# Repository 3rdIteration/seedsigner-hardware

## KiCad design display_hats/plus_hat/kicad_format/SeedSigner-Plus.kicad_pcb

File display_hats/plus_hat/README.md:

# SeedSigner Plus Display Hat

## Supporting the Project
If you are producing these to sell, please consider donating X per board to Y to support the project.

## Design Files
The files used to produce the original SeedSigner+ hat can be found in the `designspark_format` folder. This also includes production files that can be used to have the board fabricated.

A version in KiCAD format can also be found in the `kicad_format` folder along with all he files needed for low-cost economic fabrication with JLCPCB. (Very low cost if you are happy have one side assembled and manually solder the buttons on)

## LCD Display

The current design assumes LCD available here: https://www.alibaba.com/x/B1E3wJ

**LCD Specifications**
* Size: 2.8 inch
* LCD Type: IPS (A TFT cheaper TFT panel will work, but has a smaller viewing angle)
* Outline Dimensions: 47.8*66.95*2.13mm
* Number of Dots: 240(RGB)*320
* Controller: ST7789
* PIN NO.: 40P
* Display Color: RGB565
* Backlight: White LED
* Polarizer Mode: Transmissive
* Data Interface: 3/4-Wire SPI interface, MCU 8/16Bit interface
* Operating Temp.: -20 ~ 70 degree
* Storage Temp.: -30 ~ 80 degree
* Viewing Direction: 12 O’clock / Full

**Pinout for Display**
| PIN | Symbol        | Notes                                                     |
| --: | ------------- | --------------------------------------------------------- |
|   1 | XL / X−       | Resistive touch X− electrode (if resistive touch is used) |
|   2 | YU / Y−       | Resistive touch Y− electrode                              |
|   3 | XR / X+       | Resistive touch X+ electrode                              |
|   4 | YD / Y+       | Resistive touch Y+ electrode                              |
|   5 | GND           | Ground                                                    |
|   6 | VDD           | Logic supply voltage (typically 3.3 V)                    |
|   7 | VDD           | Logic supply voltage (typically 3.3 V)                    |
|   8 | TE            | Tearing Effect output (optional, frame sync signal)       |
|   9 | CSX / SPI_CS  | Chip Select for SPI or parallel interface                 |
|  10 | DCX / SPI_SCL | Data/Command select (SPI clock in SPI mode)               |
|  11 | WRX / SPI_DCX | Write strobe (parallel) or Data/Command in SPI            |
|  12 | RDX           | Read strobe (parallel interface only)                     |
|  13 | SPI_MOSI      | SPI Master Out / Slave In                                 |
|  14 | SPI_MISO      | SPI Master In / Slave Out                                 |
|  15 | RESX          | Hardware reset (active low)                               |
|  16 | GND           | Ground                                                    |
|  17 | DB0           | Parallel data bus bit 0                                   |
|  18 | DB1           | Parallel data bus bit 1                                   |
|  19 | DB2           | Parallel data bus bit 2                                   |
|  20 | DB3           | Parallel data bus bit 3                                   |
|  21 | DB4           | Parallel data bus bit 4                                   |
|  22 | DB5           | Parallel data bus bit 5                                   |
|  23 | DB6           | Parallel data bus bit 6                                   |
|  24 | DB7           | Parallel data bus bit 7                                   |
|  25 | DB8           | Parallel data bus bit 8                                   |
|  26 | DB9           | Parallel data bus bit 9                                   |
|  27 | DB10          | Parallel data bus bit 10                                  |
|  28 | DB11          | Parallel data bus bit 11                                  |
|  29 | DB12          | Parallel data bus bit 12                                  |
|  30 | DB13          | Parallel data bus bit 13                                  |
|  31 | DB14          | Parallel data bus bit 14                                  |
|  32 | DB15          | Parallel data bus bit 15                                  |
|  33 | LED-A         | Backlight LED anode (usually requires current driver)     |
|  34 | LED-K         | Backlight LED cathode                                     |
|  35 | LED-K         | Backlight LED cathode                                     |
|  36 | LED-K         | Backlight LED cathode                                     |
|  37 | GND           | Ground                                                    |
|  38 | IM0           | Interface mode select (sampled on reset)                  |
|  39 | IM1           | Interface mode select (sampled on reset)                  |
|  40 | IM2           | Interface mode select (sampled on reset)                  |

**Note: The Pin numbering on the FPC connector is in reverse order to the list above**

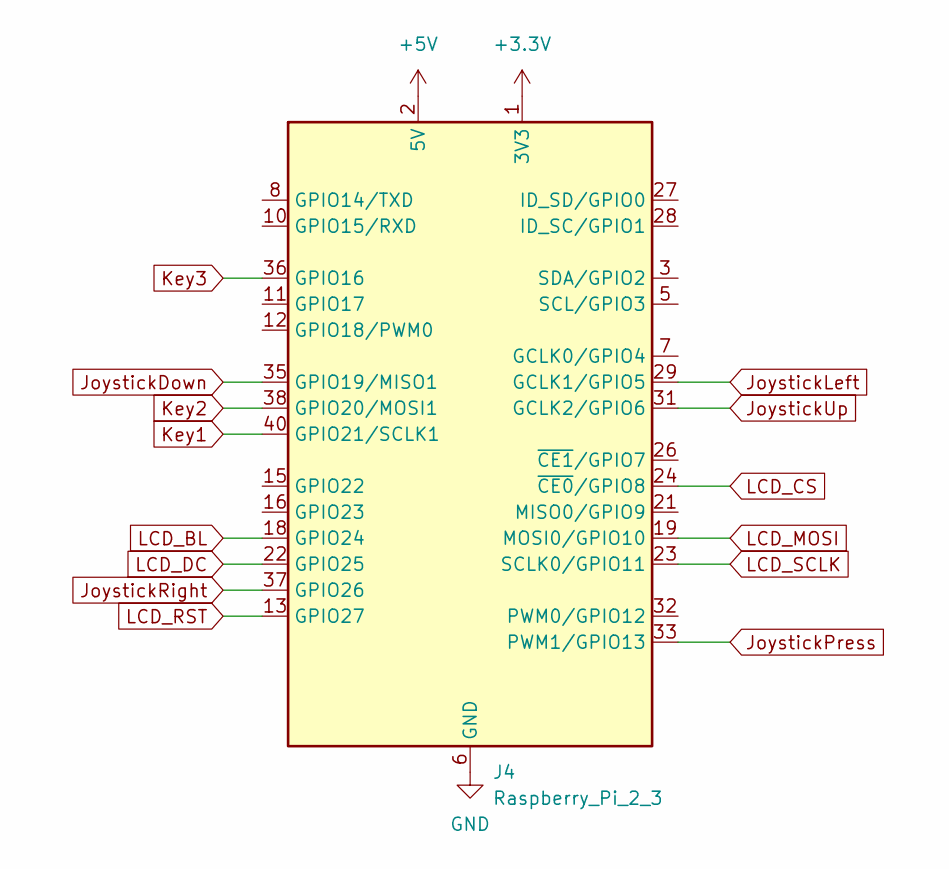
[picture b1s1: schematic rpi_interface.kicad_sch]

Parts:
J4: Raspberry_Pi_2_3; PinSocket_2x20_P2.54mm_Vertical_SMD

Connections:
+3.3V: J4.1 (3V3), J4.17 (3V3); also elsewhere on the board
+5V: J4.2 (5V), J4.4 (5V); also elsewhere on the board
GND: J4.6 (GND), J4.9 (GND), J4.14 (GND), J4.20 (GND), J4.25 (GND), J4.30 (GND), J4.34 (GND), J4.39 (GND); also elsewhere on the board
JoystickDown: J4.35 (GPIO19/MISO1); also elsewhere on the board
JoystickLeft: J4.29 (GCLK1/GPIO5); also elsewhere on the board
JoystickPress: J4.33 (PWM1/GPIO13); also elsewhere on the board
JoystickRight: J4.37 (GPIO26); also elsewhere on the board
JoystickUp: J4.31 (GCLK2/GPIO6); also elsewhere on the board
Key1: J4.40 (GPIO21/SCLK1); also elsewhere on the board
Key2: J4.38 (GPIO20/MOSI1); also elsewhere on the board
Key3: J4.36 (GPIO16); also elsewhere on the board
LCD_BL: J4.18 (GPIO24); also elsewhere on the board
LCD_CS: J4.24 (~CE0/GPIO8); also elsewhere on the board
LCD_DC: J4.22 (GPIO25); also elsewhere on the board
LCD_MOSI: J4.19 (MOSI0/GPIO10); also elsewhere on the board
LCD_RST: J4.13 (GPIO27); also elsewhere on the board
LCD_SCLK: J4.23 (SCLK0/GPIO11); also elsewhere on the board

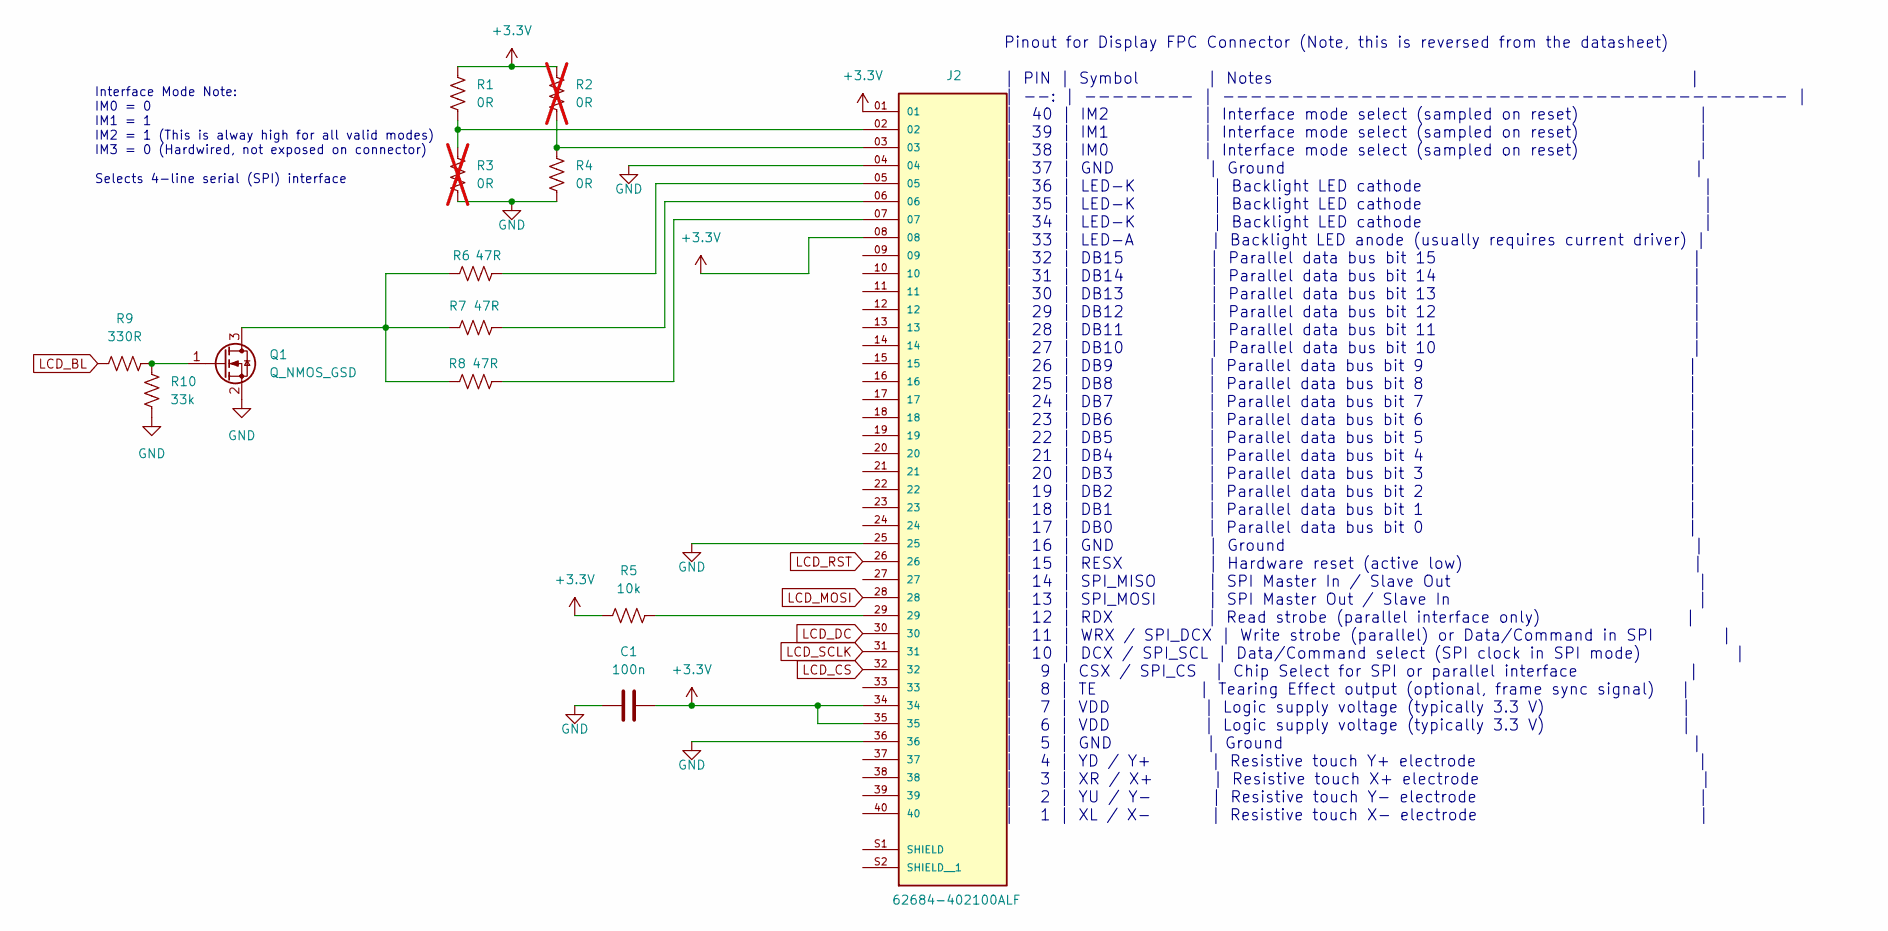
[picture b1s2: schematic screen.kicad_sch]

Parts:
C1: 100n; C_0805_2012Metric_Pad1.18x1.45mm_HandSolder
J2: 62684-402100ALF; AMPHENOL_62684-402100ALF; PARTREV AK
Q1: Q_NMOS_GSD; SOT-23
R1, R4: 0R; R_0805_2012Metric_Pad1.20x1.40mm_HandSolder
R2, R3: 0R; R_0805_2012Metric_Pad1.20x1.40mm_HandSolder; not fitted
R5: 10k; R_0805_2012Metric_Pad1.20x1.40mm_HandSolder
R6, R7, R8: 47R; R_0805_2012Metric_Pad1.20x1.40mm_HandSolder
R9: 330R; R_0805_2012Metric_Pad1.20x1.40mm_HandSolder
R10: 33k; R_0805_2012Metric_Pad1.20x1.40mm_HandSolder

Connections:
+3.3V: C1.2, J2.01, J2.08, J2.34, J2.35, R1.2, R2.2, R5.1; also elsewhere on the board
GND: C1.1, J2.04, J2.25, J2.36, Q1.2 (S), R3.2, R4.1, R10.2; also elsewhere on the board
LCD_BL: R9.2; also elsewhere on the board
LCD_CS: J2.32; also elsewhere on the board
LCD_DC: J2.30; also elsewhere on the board
LCD_MOSI: J2.28; also elsewhere on the board
LCD_RST: J2.26; also elsewhere on the board
LCD_SCLK: J2.31; also elsewhere on the board
unnamed: J2.02, R1.1, R3.1
unnamed: J2.03, R2.1, R4.2
unnamed: J2.05, R6.2
unnamed: J2.06, R7.2
unnamed: J2.07, R8.2
unnamed: J2.29, R5.2
unnamed: Q1.3 (D), R6.1, R7.1, R8.1
unnamed: Q1.1 (G), R9.1, R10.1

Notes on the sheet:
Pinout for Display FPC Connector (Note, this is reversed from the datasheet) | PIN | Symbol | Notes | | --: | -------- | ----------------------------------------- | | 40 | IM2 | Interface mode select (sampled on reset) | | 39 | IM1 | Interface mode select (sampled on reset) | | 38 | IM0 | Interface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
Interface Mode Note: IM0 = 0 IM1 = 1 IM2 = 1 (This is alway high for all valid modes) IM3 = 0 (Hardwired, not exposed on connector) Selects 4-line serial (SPI) interface

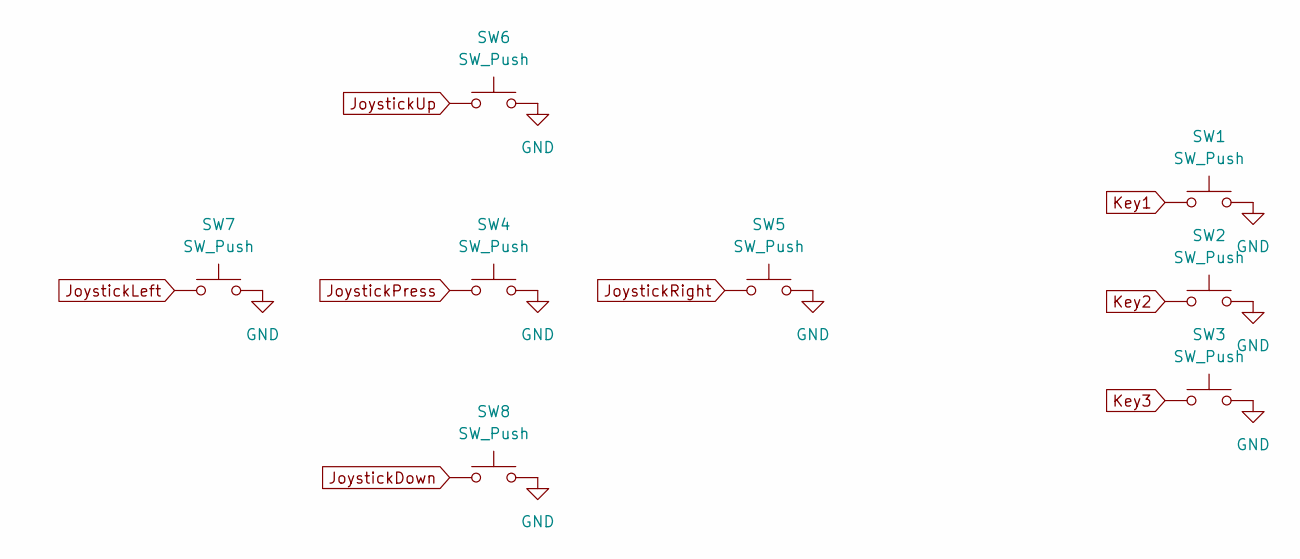
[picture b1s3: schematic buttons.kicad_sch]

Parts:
SW1, SW2, SW3, SW4, SW5, SW6, SW7, SW8: SW_Push; SW_SPST_FSMSM

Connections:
GND: SW1.2, SW2.2, SW3.2, SW4.2, SW5.2, SW6.2, SW7.2, SW8.2; also elsewhere on the board
JoystickDown: SW8.1; also elsewhere on the board
JoystickLeft: SW7.1; also elsewhere on the board
JoystickPress: SW4.1; also elsewhere on the board
JoystickRight: SW5.1; also elsewhere on the board
JoystickUp: SW6.1; also elsewhere on the board
Key1: SW1.1; also elsewhere on the board
Key2: SW2.1; also elsewhere on the board
Key3: SW3.1; also elsewhere on the board

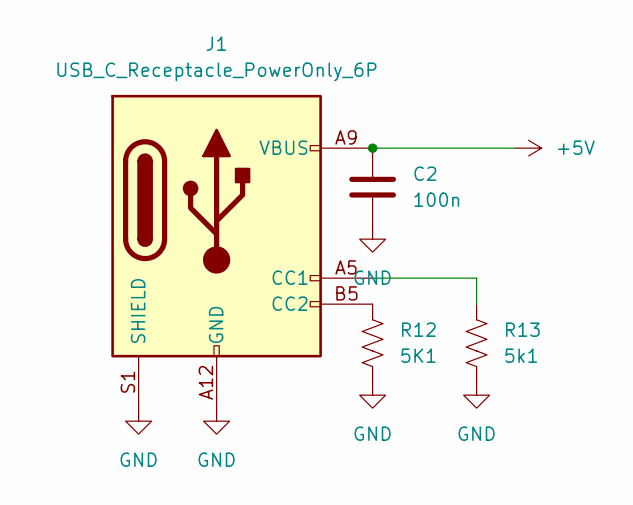
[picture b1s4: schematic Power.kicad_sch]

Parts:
C2: 100n; C_0805_2012Metric_Pad1.18x1.45mm_HandSolder
J1: USB_C_Receptacle_PowerOnly_6P; USB_C_Receptacle_HRO_TYPE-C-31-M-17
R12: 5K1; R_0805_2012Metric_Pad1.20x1.40mm_HandSolder
R13: 5k1; R_0805_2012Metric_Pad1.20x1.40mm_HandSolder

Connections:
+5V: C2.1, J1.A9 (VBUS), J1.B9 (VBUS); also elsewhere on the board
GND: C2.2, J1.A12 (GND), J1.B12 (GND), J1.S1 (SHIELD), R12.2, R13.2; also elsewhere on the board
unnamed: J1.A5 (CC1), R13.1
unnamed: J1.B5 (CC2), R12.1

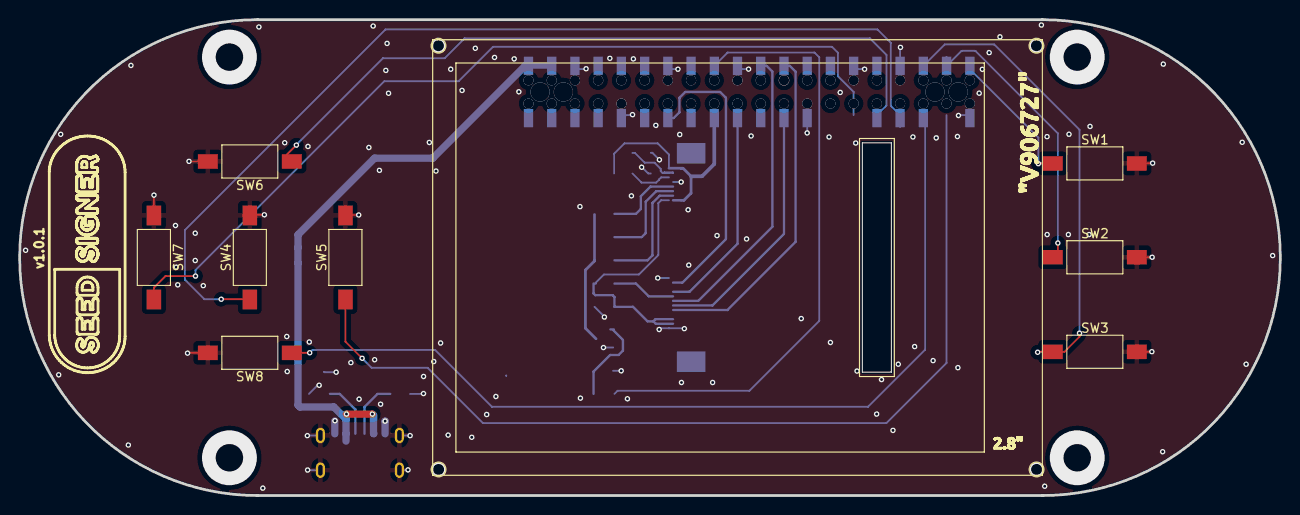
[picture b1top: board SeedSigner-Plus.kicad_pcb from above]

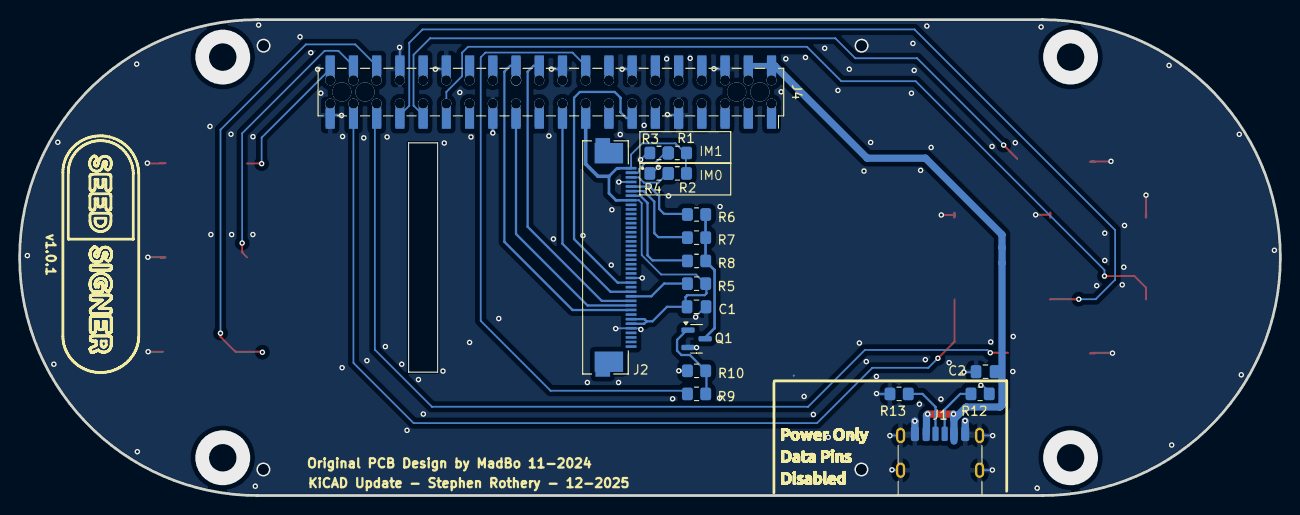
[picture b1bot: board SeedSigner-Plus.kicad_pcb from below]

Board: 2 copper layers, 137.9 x 52.0 mm, 26 parts (18 on the bottom side), 27 nets.

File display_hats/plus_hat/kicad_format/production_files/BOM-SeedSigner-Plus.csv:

Comment,Designator,Footprint,LCSC,Quantity
10k,R5,R_0805_2012Metric_Pad1.20x1.40mm_HandSolder,C17414,1
0R,"R1,R4",R_0805_2012Metric_Pad1.20x1.40mm_HandSolder,C17477,2
330R,R9,R_0805_2012Metric_Pad1.20x1.40mm_HandSolder,C17630,1
33k,R10,R_0805_2012Metric_Pad1.20x1.40mm_HandSolder,C17633,1
47R,"R6,R7,R8",R_0805_2012Metric_Pad1.20x1.40mm_HandSolder,C17714,3
Q_NMOS_GSD,Q1,SOT-23,C20917,1
62684-402100ALF,J2,AMPHENOL_62684-402100ALF,C262648,1
Raspberry_Pi_2_3,J4,PinSocket_2x20_P2.54mm_Vertical_SMD,C2685112,1
5K1,"R12,R13",R_0805_2012Metric_Pad1.20x1.40mm_HandSolder,C27834,2
SW_Push,"SW1,SW2,SW3,SW4,SW5,SW6,SW7,SW8",SW_SPST_FSMSM,C318938,8
100n,"C1,C2",C_0805_2012Metric_Pad1.18x1.45mm_HandSolder,C49678,2
USB_C_Receptacle_PowerOnly_6P,J1,USB_C_Receptacle_HRO_TYPE-C-31-M-17,C668623,1

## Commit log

2025-12-07 Add enclosure files
    Batch add enclosure files from main repo
2025-12-07 Add SeedQR templates
    Add seedqr templates and cleanup
2025-12-07 Add SeedSigner Plus Hat designspark version
    Add SeedSigner Plus Hat designspark version
2025-12-14 Add some extra docco
2025-12-14 Fix formatting in README.md for Plus Display Hat
2025-12-18 Add SeedSigner Plus enclosure files
    Includes printable .3mf files and the Fusion360 versions of the enclosure
2026-01-02 Add KiCAD version
    Re-created in KiCAD for easy editing and long term support. (Lightly modified PCB routing, position of main components, ports, etc, unchanged.)
